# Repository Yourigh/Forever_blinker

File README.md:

# Forever_blinker
Electronics design that blinks a LED for months on AA battery

# Current state
Blinker esign is tested and works well. 
ATTINY variant was not verified.

# Power supply
Boost converter is used to create 3.3 V (handles about 30mA load) and has low Iq. (<20uA)

# Two options
Primary assembly option is an op-amp oscillator. Tested and working.

Another option is to use ATTINY85 and program it to do the same job. (not elaborated in this repository yet)

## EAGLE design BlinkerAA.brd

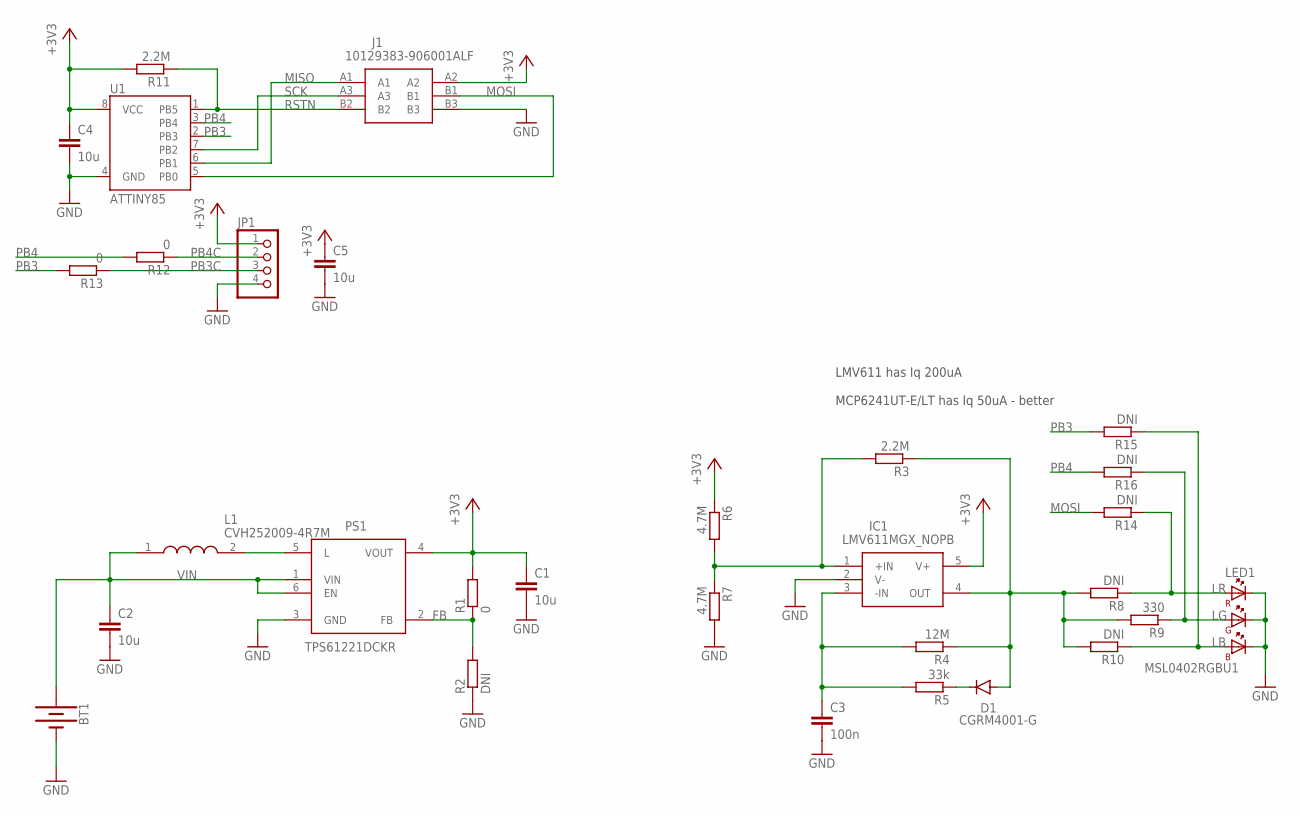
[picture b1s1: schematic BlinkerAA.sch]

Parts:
BT1: BATTERY-AA
C1, C2, C4, C5: 10u; C0603K; PARTNO GRM188R61A106KE69J
C3: 100n; C0603K; PARTNO GRM188R61A106KE69J
D1: CGRM4001-G; SOD-123_MINI-SMA
IC1: LMV611MGX_NOPB; SOT65P210X110-5N
J1: 10129383-906001ALF; 10129383906001ALF
JP1: PINHD-1X4; 1X04
L1: CVH252009-4R7M; INDC2520X100N
LED1: MSL0402RGBU1
PS1: TPS61221DCKR; SOT65P210X110-6N
R1, R12, R13: 0; R0603
R2, R8, R10, R14, R15, R16: DNI; R0603
R3, R11: 2.2M; R0603
R4: 12M; R0603
R5: 33k; R0603
R6, R7: 4.7M; R0603
R9: 330; R0603
U1: ATTINY85

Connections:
+3V3: C1.1, C4.1, C5.1, IC1.5 (V+), J1.A2, JP1.1, PS1.4 (VOUT), R1.2, R6.1, R11.2, U1.8 (VCC)
FB: PS1.2 (FB), R1.1, R2.2
GND: BT1.GND@1 (-), C1.2, C2.2, C3.2, C4.2, C5.2, IC1.2 (V-), J1.B3, JP1.4, LED1.1 (K_B), LED1.2 (K_G), LED1.3 (K_R), PS1.3 (GND), R2.1, R7.2, U1.4 (GND)
LB: LED1.6 (A_B), R10.1, R15.1
LG: LED1.5 (A_G), R9.1, R16.1
LR: LED1.4 (A_R), R8.1, R14.1
MISO: J1.A1, U1.6 (PB1)
MOSI: J1.B1, R14.2, U1.5 (PB0)
unnamed: IC1.1 (+IN), R3.2, R6.2, R7.1
unnamed: L1.2, PS1.5 (L)
unnamed: D1.A, IC1.4 (OUT), R3.1, R4.1, R8.2, R9.2, R10.2
unnamed: C3.1, IC1.3 (-IN), R4.2, R5.2
unnamed: D1.C, R5.1
PB3: R13.2, R15.2, U1.2 (PB3)
PB3C: JP1.3, R13.1
PB4: R12.2, R16.2, U1.3 (PB4)
PB4C: JP1.2, R12.1
RSTN: J1.B2, R11.1, U1.1 (PB5)
SCK: J1.A3, U1.7 (PB2)
VIN: BT1.PWR@1 (+), C2.1, L1.1, PS1.1 (VIN), PS1.6 (EN)

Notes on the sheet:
LMV611 has Iq 200uA MCP6241UT-E/LT has Iq 50uA - better

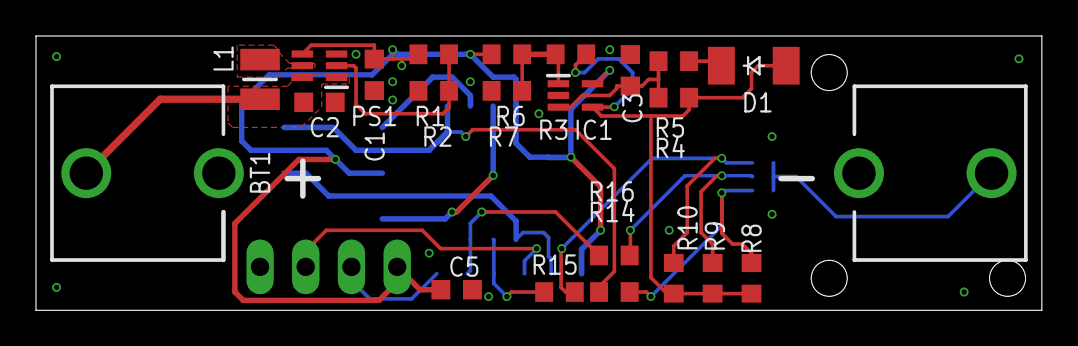
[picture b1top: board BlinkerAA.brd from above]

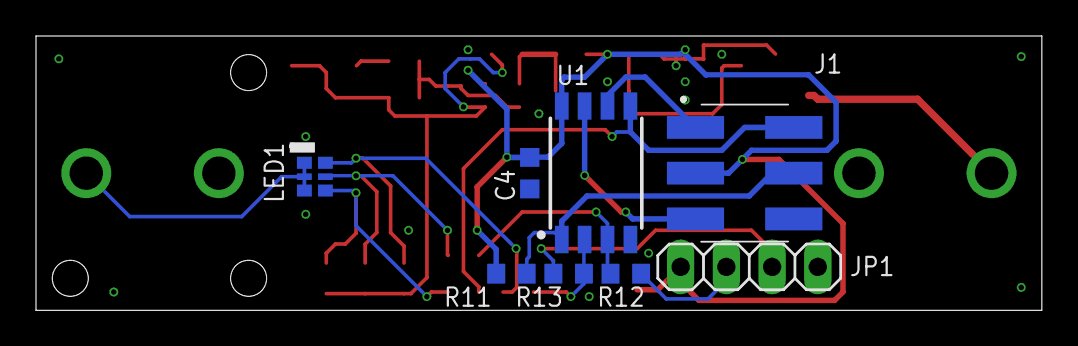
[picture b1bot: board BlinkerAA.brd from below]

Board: 2 copper layers, 55.9 x 15.2 mm, 30 parts (8 on the bottom side), 20 nets.

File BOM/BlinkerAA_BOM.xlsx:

POWER SUPPLY AND COMMON
Qty | Value | Part Num | Package | Parts
2 |  | 534-092 | BATTERY-AA | BT1 | https://eu.mouser.com/ProductDetail/Keystone-Electronics/92?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
1 | CVH252009-4R7M | CVH252009-4R7M | INDC2520X100N | L1 | https://eu.mouser.com/ProductDetail/Bourns/CVH252009-4R7M?qs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
1 | TPS61221DCKR | TPS61221DCKR | SOT65P210X110-6N | PS1 | https://eu.mouser.com/ProductDetail/Texas-Instruments/TPS612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
2 | 10u | GRM188R61A106KE69J | C0603K | C1, C2, C4, C5 | stock
1 | MSL0402RGBU1 | MSL0402RGBU1 | MSL0402RGBU1 | LED1 | stock
1 | 0 | * | R0603 | R1 | stock
1 | DNI | * | R0603 | R2 | stock
AT-TINY variant
1 |  | * | 1X04 | JP1 | stock
1 | ATTINY85 | ATTINY85-20SU | ATTINY85 | U1 | https://eu.mouser.com/ProductDetail/Microchip-Technology-Atm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
1 | 2.2M | * | R0603 | R11 | stock
2 | 10u | GRM188R61A106KE69J | C0603K | C4, C5 | stock
2 | 0 | * | R0603 | R12, R13 | stock
1 | 10129383-906001ALF | 10129383-906001ALF | 10129383906001ALF | J1 | https://eu.mouser.com/ProductDetail/Amphenol-FCI/10129383-90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
3 | DNI | * | R0603 | R14, R15, R16 | stock - LED bias
OP-AMP blinker variant
1 | LMV611MGX_NOPB | LMV611MGX/NOPB or MCP6241UT-E/LT | SOT65P210X110-5N | IC1 | https://eu.mouser.com/ProductDetail/Microchip-Technology/MCP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
1 | CGRM4001-G | * | SOD-123_MINI-SMA | D1 | https://eu.mouser.com/ProductDetail/Diodes-Incorporated/MMBD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
1 | 33k | * | R0603 | R5
1 | 12M | * | R0603 | R4
1 | 100n | GRM188R61A106KE69J | C0603K | C3
2 | 4.7M | * | R0603 | R6, R7
1 | 2.2M | * | R0603 | R3
1 | 330 | * | R0603 | R9
2 | DNI | * | R0603 | R8, R10
https://eu.mouser.com/ProjectManager/ProjectDetail.aspx?Acce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

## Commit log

2019-10-29 schematics done
2019-11-01 gerbers generation, readme update

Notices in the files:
parts and their libraries:
SparkFun-Batteries: Licensing: Creative Commons ShareAlike 4.0 International - https://creativecommons.org/licenses/by-sa/4.0
